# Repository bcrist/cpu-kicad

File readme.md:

This repo contains KiCAD design files for my hobby discrete-logic CPU.

You can find the main repo here: https://github.com/bcrist/cpu

This repo is kept separately because KiCAD files tend to get very large, and I want to be able to ensure that the main repo doesn't get bloated with them.  The main repo instead has this repo as a shallow submodule.  Yes, I could have just used LFS instead, but I'd rather it be completely separate.

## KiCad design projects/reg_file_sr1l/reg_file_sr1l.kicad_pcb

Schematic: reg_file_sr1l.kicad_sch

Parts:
C1, C6: 10u; C_0805
C2, C5, C7, C10: 100n; C_0402
C3, C4, C8, C9: 22u; C_0805
J1, J2, J3: 2M11_2M71; CardEdge_PCIe_x16
L1, L2: 3.3u; L_taiyo_yuden_nrs5040
Q1, Q2: 2N3904; U_TO92-3
R1: 33k2 1%; R_0402
R2, R6: 10k 1%; R_0402
R3, R7: LIST; R_0402
R4, R8: 15m; R_1206
R5: 56k2 1%; R_0402
R9, R10, R11, R12: 1k; R_0402
U1, U3: AP62300TWU-7; U_SOT23-6
U2, U4: EMC1702; U_QFN-12_4x4_P0.8_EP2.1x2.1
U5, U7, U24: 74LVC1G86; U_SOT353_1.25x2.1_P0.65
U6, U12: 74LVC1G157; U_SOT363_1.25x2.1_P0.65
U8, U9: CY7C0241-15AC; U_QFP-100_14x14_P0.5
U10: 74LVC139; U_TSSOP-16_4.4x5_P0.65
U11: 74LVC138; U_TSSOP-16_4.4x5_P0.65
U13: 74LVCH16244A; U_TVSOP-48_4.4x9.7_P0.4
U14, U15: 74LVT16244; U_TVSOP-48_4.4x9.7_P0.4
U16: 74LVCH16374; U_TSSOP-48_6.1x12.5_P0.5
U17, U18: 74LVC574; U_TSSOP-20_4.4x6.5_P0.65
U19, U20, U21, U22: 74LVC541; U_TSSOP-20_4.4x6.5_P0.65
U23: 74LVC1G02; U_SOT353_1.25x2.1_P0.65
U25: 74LVC1G332; U_SOT363_1.25x2.1_P0.65

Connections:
+5V: R8.1, U4.11 (SENSE-), U6.3, U8.12 (+5V), U8.17 (+5V), U8.36 (~ROE), U8.39 (~RSEM), U8.62 (M~S), U8.86 (~LSEM), U8.87 (~LWE), U8.88 (+5V), U9.12 (+5V), U9.17 (+5V), U9.36 (~ROE), U9.39 (~RSEM), U9.62 (M~S), U9.86 (~LSEM), U9.87 (~LWE), U9.88 (+5V), U11.6, U12.3
+12V: C1.1, C6.1, J1.A1, J1.A2, J1.A3, J1.B1, J1.B2, J1.B3, U1.3 (VIN), U3.3 (VIN)
/3v3: C3.1, C4.1, C5.1, L1.1, R1.1, R4.2, U2.1 (VDD), U2.12 (SENSE+)
/5v0: C8.1, C9.1, C10.1, L2.1, R5.1, R8.2, U4.1 (VDD), U4.12 (SENSE+)
/PHI: U16.25 (CLK), U16.48 (CLK), U17.11, U18.11, U25.3
/RD_{0}: U9.90 (LD0), U14.47 (A0), U15.47 (A0), U16.47 (A0)
/RD_{1}: U9.91 (LD1), U14.46 (A1), U15.46 (A1), U16.46 (A1)
/RD_{2}: U9.93 (LD2), U14.44 (A2), U15.44 (A2), U16.44 (A2)
/RD_{3}: U9.94 (LD3), U14.43 (A3), U15.43 (A3), U16.43 (A3)
/RD_{4}: U9.95 (LD4), U14.41 (A4), U15.41 (A4), U16.41 (A4)
/RD_{5}: U9.96 (LD5), U14.40 (A5), U15.40 (A5), U16.40 (A5)
/RD_{6}: U9.97 (LD6), U14.38 (A6), U15.38 (A6), U16.38 (A6)
/RD_{7}: U9.98 (LD7), U14.37 (A7), U15.37 (A7), U16.37 (A7)
/RD_{8}: U9.3 (LD8), U14.36 (A4), U15.36 (A4), U16.36 (A4)
/RD_{9}: U9.4 (LD17), U14.35 (A5), U15.35 (A5), U16.35 (A5)
/RD_{10}: U9.5 (LD11), U14.33 (A6), U15.33 (A6), U16.33 (A6)
/RD_{11}: U9.6 (LD12), U14.32 (A7), U15.32 (A7), U16.32 (A7)
/RD_{12}: U9.7 (LD13), U14.30 (A4), U15.30 (A4), U16.30 (A4)
/RD_{13}: U9.8 (LD14), U14.29 (A5), U15.29 (A5), U16.29 (A5)
/RD_{14}: U9.10 (LD15), U14.27 (A6), U15.27 (A6), U16.27 (A6)
/RD_{15}: U9.11 (LD16), U14.26 (A7), U15.26 (A7), U16.26 (A7)
/S.A_BASE_{0}: J1.A24, U13.2 (Y0)
/S.A_BASE_{1}: J1.A25, U13.3 (Y1)
/S.A_BASE_{2}: J1.A26, U13.5 (Y2)
/S.A_BASE_{3}: J1.A27, U13.6 (Y3)
/S.A_BASE_{4}: J1.A28, U13.8 (Y4)
/S.A_BASE_{5}: J1.A29, U13.9 (Y5)
/S.A_BASE_{6}: J1.A30, U13.11 (Y6)
/S.A_BASE_{7}: J1.A31, U13.12 (Y7)
/S.A_BASE_{8}: J1.A32, U13.13 (Y4)
/S.A_BASE_{9}: J1.A33, U13.14 (Y5)
/S.A_BASE_{10}: J1.A34, U13.16 (Y6)
/S.A_BASE_{11}: J1.A35, U13.17 (Y7)
/S.A_BASE_{12}: J1.A36, U13.19 (Y4)
/S.A_BASE_{13}: J1.A37, U13.20 (Y5)
/S.A_BASE_{14}: J1.A38, U13.22 (Y6)
/S.A_BASE_{15}: J1.A39, U13.23 (Y7)
/S.BASE_{0}: U8.66 (LA0)
/S.BASE_{1}: U8.67 (LA1)
/S.BASE_{2}: U8.68 (LA2)
/S.BASE_{3}: U6.6, U12.6
/S.FX_OVR_R_BASE: U5.1
/S.FX_OVR_R_SR1: U7.1
/S.FX_OVR_W: U24.1
/S.JL_SRC_{0}: U10.2
/S.JL_SRC_{1}: U10.3
/S.JL_{0}: J3.A57, U14.2 (Y0)
/S.JL_{1}: J3.A56, U14.3 (Y1)
/S.JL_{2}: J3.A55, U14.5 (Y2)
/S.JL_{3}: J3.A54, U14.6 (Y3)
/S.JL_{4}: J3.A53, U14.8 (Y4)
/S.JL_{5}: J3.A52, U14.9 (Y5)
/S.JL_{6}: J3.A51, U14.11 (Y6)
/S.JL_{7}: J3.A50, U14.12 (Y7)
/S.JL_{8}: J3.A49, U14.13 (Y4)
/S.JL_{9}: J3.A48, U14.14 (Y5)
/S.JL_{10}: J3.A47, U14.16 (Y6)
/S.JL_{11}: J3.A46, U14.17 (Y7)
/S.JL_{12}: J3.A45, U14.19 (Y4)
/S.JL_{13}: J3.A44, U14.20 (Y5)
/S.JL_{14}: J3.A43, U14.22 (Y6)
/S.JL_{15}: J3.A42, U14.23 (Y7)
/S.K_SRC_{0}: U11.1
/S.K_SRC_{1}: U11.2
/S.K_SRC_{2}: U11.3
/S.K_{0}: J3.A35, U15.2 (Y0)
/S.K_{1}: J3.A34, U15.3 (Y1)
/S.K_{2}: J3.A33, U15.5 (Y2)
/S.K_{3}: J3.A32, U15.6 (Y3)
/S.K_{4}: J3.A31, U15.8 (Y4)
/S.K_{5}: J3.A30, U15.9 (Y5)
/S.K_{6}: J3.A29, U15.11 (Y6)
/S.K_{7}: J3.A28, U15.12 (Y7)
/S.K_{8}: J3.A27, U15.13 (Y4)
/S.K_{9}: J3.A26, U15.14 (Y5)
/S.K_{10}: J3.A25, U15.16 (Y6)
/S.K_{11}: J3.A24, U15.17 (Y7)
/S.K_{12}: J3.A23, U15.19 (Y4)
/S.K_{13}: J3.A22, U15.20 (Y5)
/S.K_{14}: J3.A21, U15.22 (Y6)
/S.K_{15}: J3.A20, U15.23 (Y7)
/S.RCTX_{0}: U8.69 (LA3), U9.69 (LA3)
/S.RCTX_{1}: U8.70 (LA4), U9.70 (LA4)
/S.RCTX_{2}: U8.71 (LA5), U9.71 (LA5)
/S.RCTX_{3}: U8.76 (LA6), U9.76 (LA6)
/S.RCTX_{4}: U8.77 (LA7), U9.77 (LA7)
/S.RCTX_{5}: U8.78 (LA8), U9.78 (LA8)
/S.SR1_RI_{0}: U9.66 (LA0)
/S.SR1_RI_{1}: U9.67 (LA1)
/S.SR1_RI_{2}: U9.68 (LA2)
/SCL: J1.B5, U2.8 (SCL), U4.8 (SCL)
/SDA: J1.B6, U2.7 (SDA), U4.7 (SDA)
/SLEEPING: U6.1, U8.40 (~RCE), U9.40 (~RCE), U9.85 (~LCE)
/SW3v3: C2.2, L1.2, U1.2 (SW)
/SW5v0: C7.2, L2.2, U3.2 (SW)
/T.INHIBIT_W: U25.1
/T.L_{0}: J2.A61, U19.2 (A0)
/T.L_{1}: J2.A60, U19.3 (A1)
/T.L_{2}: J2.A59, U19.4 (A2)
/T.L_{3}: J2.A58, U19.5 (A3)
/T.L_{4}: J2.A57, U19.6 (A4)
/T.L_{5}: J2.A56, U19.7 (A5)
/T.L_{6}: J2.A55, U19.8 (A6)
/T.L_{7}: J2.A54, U19.9 (A7)
/T.L_{8}: J2.A53, U20.2 (A0)
/T.L_{9}: J2.A52, U20.3 (A1)
/T.L_{10}: J2.A51, U20.4 (A2)
/T.L_{11}: J2.A50, U20.5 (A3)
/T.L_{12}: J2.A49, U20.6 (A4)
/T.L_{13}: J2.A48, U20.7 (A5)
/T.L_{14}: J2.A47, U20.8 (A6)
/T.L_{15}: J2.A46, U20.9 (A7)
/T.N_{0}: J1.A53, U21.2 (A0)
/T.N_{1}: J1.A54, U21.3 (A1)
/T.N_{2}: J1.A55, U21.4 (A2)
/T.N_{3}: J1.A56, U21.5 (A3)
/T.N_{4}: J1.A57, U21.6 (A4)
/T.N_{5}: J1.A58, U21.7 (A5)
/T.N_{6}: J1.A59, U21.8 (A6)
/T.N_{7}: J1.A60, U21.9 (A7)
/T.N_{8}: J1.A61, U22.2 (A0)
/T.N_{9}: J1.A62, U22.3 (A1)
/T.N_{10}: J1.A63, U22.4 (A2)
/T.N_{11}: J1.A64, U22.5 (A3)
/T.P_{0}: J1.A65, U22.6 (A4)
/T.P_{1}: J1.A66, U22.7 (A5)
/T.P_{2}: J1.A67, U22.8 (A6)
/T.P_{3}: J1.A68, U22.9 (A7)
/T.RCTX_{0}: U8.56 (RA3), U9.56 (RA3)
/T.RCTX_{1}: U8.55 (RA4), U9.55 (RA4)
/T.RCTX_{2}: U8.50 (RA5), U9.50 (RA5)
/T.RCTX_{3}: U8.49 (RA6), U9.49 (RA6)
/T.RCTX_{4}: U8.48 (RA7), U9.48 (RA7)
/T.RCTX_{5}: U8.47 (RA8), U9.47 (RA8)
/T.SR1_WI_{0}: U8.59 (RA0), U9.59 (RA0)
/T.SR1_WI_{1}: U8.58 (RA1), U9.58 (RA1)
/T.SR1_WI_{2}: U8.57 (RA2), U9.57 (RA2)
/T.SR1_WSRC_{0}: U10.14, U23.1
/T.SR1_WSRC_{1}: U10.13, U23.2
/WD_{0}: U8.14 (RD0), U9.14 (RD0), U17.19 (Q0), U19.18 (Y0), U21.18 (Y0)
/WD_{1}: U8.15 (RD1), U9.15 (RD1), U17.18 (Q1), U19.17 (Y1), U21.17 (Y1)
/WD_{2}: U8.16 (RD2), U9.16 (RD2), U17.17 (Q2), U19.16 (Y2), U21.16 (Y2)
/WD_{3}: U8.18 (RD3), U9.18 (RD3), U17.16 (Q3), U19.15 (Y3), U21.15 (Y3)
/WD_{4}: U8.19 (RD4), U9.19 (RD4), U17.15 (Q4), U19.14 (Y4), U21.14 (Y4)
/WD_{5}: U8.20 (RD5), U9.20 (RD5), U17.14 (Q5), U19.13 (Y5), U21.13 (Y5)
/WD_{6}: U8.21 (RD6), U9.21 (RD6), U17.13 (Q6), U19.12 (Y6), U21.12 (Y6)
/WD_{7}: U8.26 (RD7), U9.26 (RD7), U17.12 (Q7), U19.11 (Y7), U21.11 (Y7)
/WD_{8}: U8.22 (RD8), U9.22 (RD8), U18.19 (Q0), U20.18 (Y0), U22.18 (Y0)
/WD_{9}: U8.23 (RD17), U9.23 (RD17), U18.18 (Q1), U20.17 (Y1), U22.17 (Y1)
/WD_{10}: U8.29 (RD11), U9.29 (RD11), U18.17 (Q2), U20.16 (Y2), U22.16 (Y2)
/WD_{11}: U8.30 (RD12), U9.30 (RD12), U18.16 (Q3), U20.15 (Y3), U22.15 (Y3)
/WD_{12}: U8.31 (RD13), U9.31 (RD13), U18.15 (Q4), U20.14 (Y4), U22.14 (Y4)
/WD_{13}: U8.32 (RD14), U9.32 (RD14), U18.14 (Q5), U20.13 (Y5), U22.13 (Y5)
/WD_{14}: U8.33 (RD15), U9.33 (RD15), U18.13 (Q6), U20.12 (Y6), U22.12 (Y6)
/WD_{15}: U8.35 (RD16), U9.35 (RD16), U18.12 (Q7), U20.11 (Y7), U22.11 (Y7)
/WFX: U8.46 (RA9), U9.46 (RA9), U24.4
/~PHI: U10.1, U11.4, U12.1
/~RESETod: J1.A7
/~WE: U8.37 (~RWE), U9.37 (~RWE), U25.4
/~WRITE_FROM_L: U10.10, U19.1 (~OE), U20.1 (~OE)
/~WRITE_FROM_PN: U10.9, U21.1 (~OE), U22.1 (~OE)
/~WRITE_FROM_SELF: U10.11, U17.1 (~OE), U18.1 (~OE)
GND: C1.2, C3.2, C4.2, C5.2, C6.2, C8.2, C9.2, C10.2, J1.A4, J1.A5, J1.A6, J1.B4, J1.B7, R2.2, R3.2, R6.2, R7.2, R9.2, R10.2, R11.2, R12.2, U1.1 (GND), U2.EP (GND), U3.1 (GND), U4.EP (GND), U5.3 (GND), U6.2 (GND), U7.3 (GND), U8.9 (GND), U8.13 (GND), U8.34 (GND), U8.38 (GND), U8.41 (~RHE), U8.42 (~RLE), U8.44 (RA11), U8.45 (RA10), U8.63 (GND), U8.80 (LA10), U8.81 (LA11), U8.83 (~LLE), U8.84 (~LHE), U8.89 (~LOE), U8.92 (GND), U9.9 (GND), U9.13 (GND), U9.34 (GND), U9.38 (GND), U9.41 (~RHE), U9.42 (~RLE), U9.44 (RA11), U9.45 (RA10), U9.63 (GND), U9.80 (LA10), U9.81 (LA11), U9.83 (~LLE), U9.84 (~LHE), U9.89 (~LOE), U9.92 (GND), U10.8 (GND), U10.15, U11.5, U11.8 (GND), U12.2 (GND), U13.4 (GND), U13.10 (GND), U13.15 (GND), U13.21 (GND), U13.28 (GND), U13.34 (GND), U13.39 (GND), U13.45 (GND), U14.4 (GND), U14.10 (GND), U14.15 (GND), U14.21 (GND), U14.28 (GND), U14.34 (GND), U14.39 (GND), U14.45 (GND), U15.4 (GND), U15.10 (GND), U15.15 (GND), U15.21 (GND), U15.28 (GND), U15.34 (GND), U15.39 (GND), U15.45 (GND), U16.1 (~OE), U16.4 (GND), U16.10 (GND), U16.15 (GND), U16.21 (GND), U16.24 (~OE), U16.28 (GND), U16.34 (GND), U16.39 (GND), U16.45 (GND), U17.10 (GND), U18.10 (GND), U19.10 (GND), U19.19 (~OE), U20.10 (GND), U20.19 (~OE), U21.10 (GND), U21.19 (~OE), U22.10 (GND), U22.19 (~OE), U23.3 (GND), U24.3 (GND), U25.2 (GND)
unnamed: C2.1, U1.6 (BST)
unnamed: C7.1, U3.6 (BST)
unnamed: Q1.1 (E), U2.3 (DN)
unnamed: Q1.2 (B), Q1.3 (C), U2.2 (DP)
unnamed: Q2.1 (E), U4.3 (DN)
unnamed: Q2.2 (B), Q2.3 (C), U4.2 (DP)
unnamed: R1.2, R2.1, U1.4 (FB)
unnamed: R3.1, U2.4 (ADDR)
unnamed: R5.2, R6.1, U3.4 (FB)
unnamed: R7.1, U4.4 (ADDR)
unnamed: R9.1, U8.27 (RD9)
unnamed: R10.1, U8.28 (RD10)
unnamed: R11.1, U9.27 (RD9)
unnamed: R12.1, U9.28 (RD10)
unnamed: U5.4, U8.79 (LA9)
unnamed: U6.4, U8.85 (~LCE)
unnamed: U7.4, U9.79 (LA9)
unnamed: U10.6, U14.1 (~OE), U14.24 (~OE), U14.25 (~OE), U14.48 (~OE)
unnamed: U11.13, U15.1 (~OE), U15.24 (~OE), U15.25 (~OE), U15.48 (~OE)
unnamed: U12.4, U13.1 (~OE), U13.24 (~OE), U13.25 (~OE), U13.48 (~OE)
unnamed: U8.11 (LD16), U13.26 (A7)
unnamed: U8.10 (LD15), U13.27 (A6)
unnamed: U8.8 (LD14), U13.29 (A5)
unnamed: U8.7 (LD13), U13.30 (A4)
unnamed: U8.6 (LD12), U13.32 (A7)
unnamed: U8.5 (LD11), U13.33 (A6)
unnamed: U8.4 (LD17), U13.35 (A5)
unnamed: U8.3 (LD8), U13.36 (A4)
unnamed: U8.98 (LD7), U13.37 (A7)
unnamed: U8.97 (LD6), U13.38 (A6)
unnamed: U8.96 (LD5), U13.40 (A5)
unnamed: U8.95 (LD4), U13.41 (A4)
unnamed: U8.94 (LD3), U13.43 (A3)
unnamed: U8.93 (LD2), U13.44 (A2)
unnamed: U8.91 (LD1), U13.46 (A1)
unnamed: U8.90 (LD0), U13.47 (A0)
unnamed: U16.2 (Y0), U17.2 (D0)
unnamed: U16.3 (Y1), U17.3 (D1)
unnamed: U16.5 (Y2), U17.4 (D2)
unnamed: U16.6 (Y3), U17.5 (D3)
unnamed: U16.8 (Y4), U17.6 (D4)
unnamed: U16.9 (Y5), U17.7 (D5)
unnamed: U16.11 (Y6), U17.8 (D6)
unnamed: U16.12 (Y7), U17.9 (D7)
unnamed: U16.13 (Y4), U18.2 (D0)
unnamed: U16.14 (Y5), U18.3 (D1)
unnamed: U16.16 (Y6), U18.4 (D2)
unnamed: U16.17 (Y7), U18.5 (D3)
unnamed: U16.19 (Y4), U18.6 (D4)
unnamed: U16.20 (Y5), U18.7 (D5)
unnamed: U16.22 (Y6), U18.8 (D6)
unnamed: U16.23 (Y7), U18.9 (D7)
unnamed: U23.4, U25.6
VCC: R4.1, U2.11 (SENSE-), U5.5 (VCC), U6.5 (VCC), U7.5 (VCC), U10.16 (VCC), U11.16 (VCC), U12.5 (VCC), U13.7 (VCC), U13.18 (VCC), U13.31 (VCC), U13.42 (VCC), U14.7 (VCC), U14.18 (VCC), U14.31 (VCC), U14.42 (VCC), U15.7 (VCC), U15.18 (VCC), U15.31 (VCC), U15.42 (VCC), U16.7 (VCC), U16.18 (VCC), U16.31 (VCC), U16.42 (VCC), U17.20 (VCC), U18.20 (VCC), U19.20 (VCC), U20.20 (VCC), U21.20 (VCC), U22.20 (VCC), U23.5 (VCC), U24.5 (VCC), U25.5 (VCC)

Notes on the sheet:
Taiyo Yuden NRS5040T3R3NMGJ
LIST (5%) 0 100 180 300 430 560 750 1k27 1k6 2k 2k7 3k6 5k6 open
Susumu KRL1632E-M-R015-F-T5
TL = TQ
Address 0x4C 0x4D 0x4E 0x4F 0x48 0x49 0x4A 0x4B 0x28 0x29 0x2A 0x2B 0x2C 0x18

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
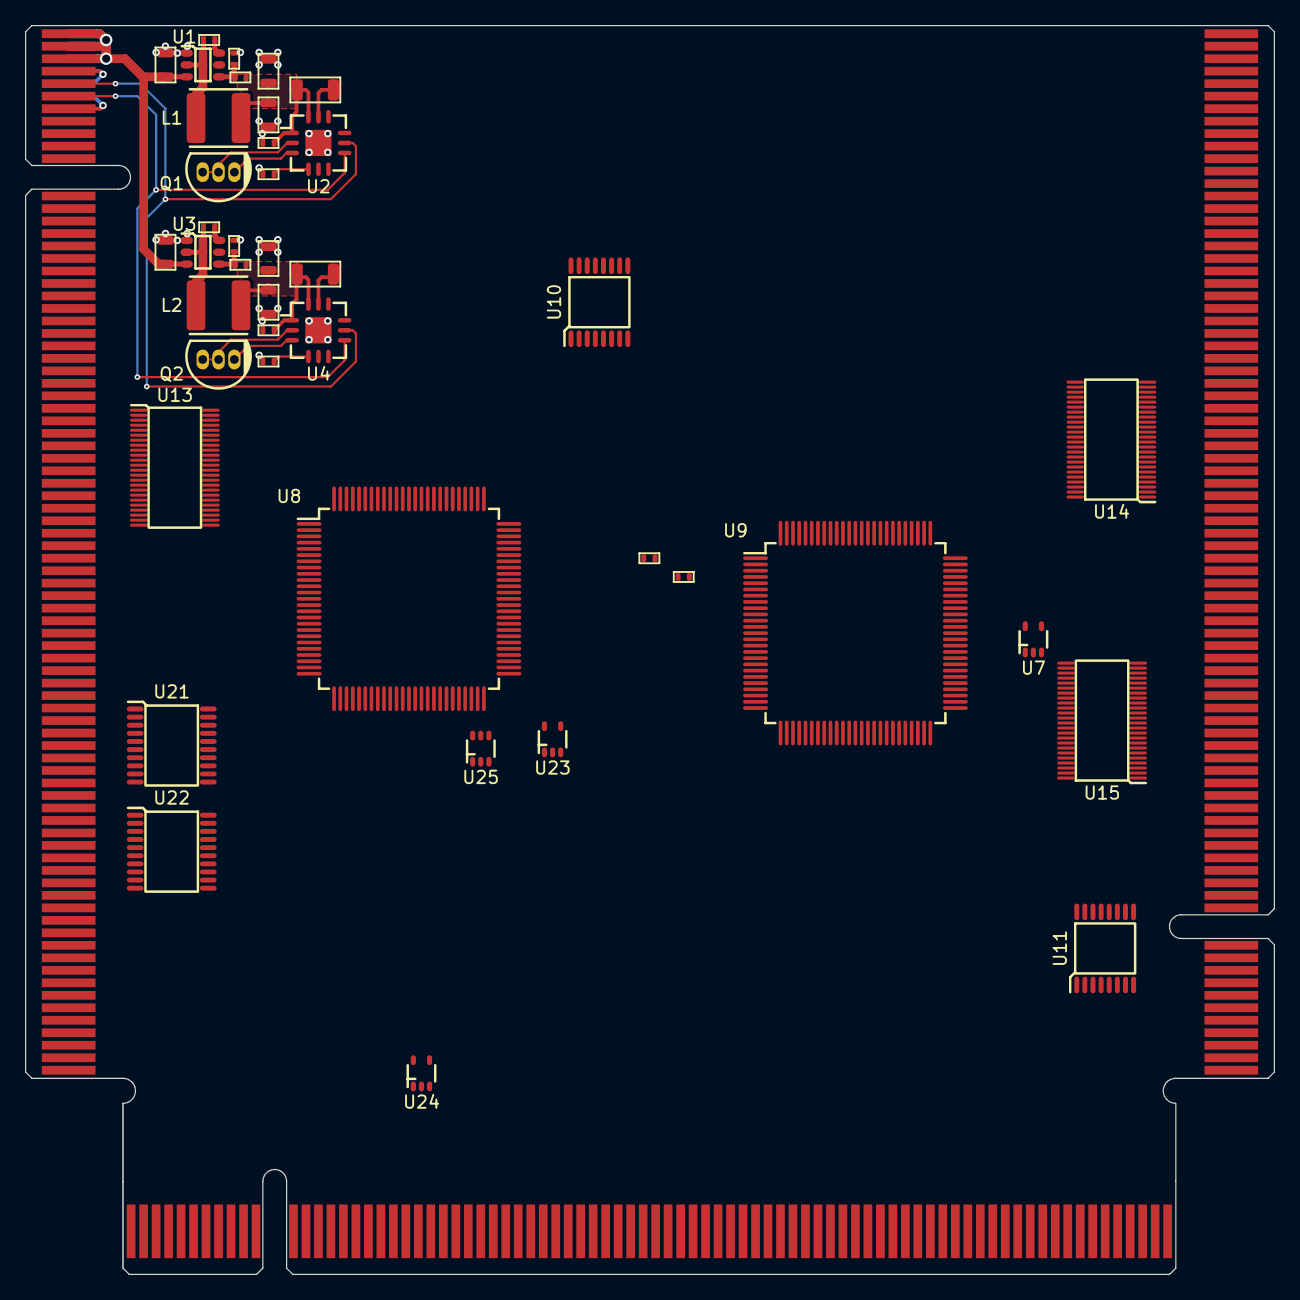
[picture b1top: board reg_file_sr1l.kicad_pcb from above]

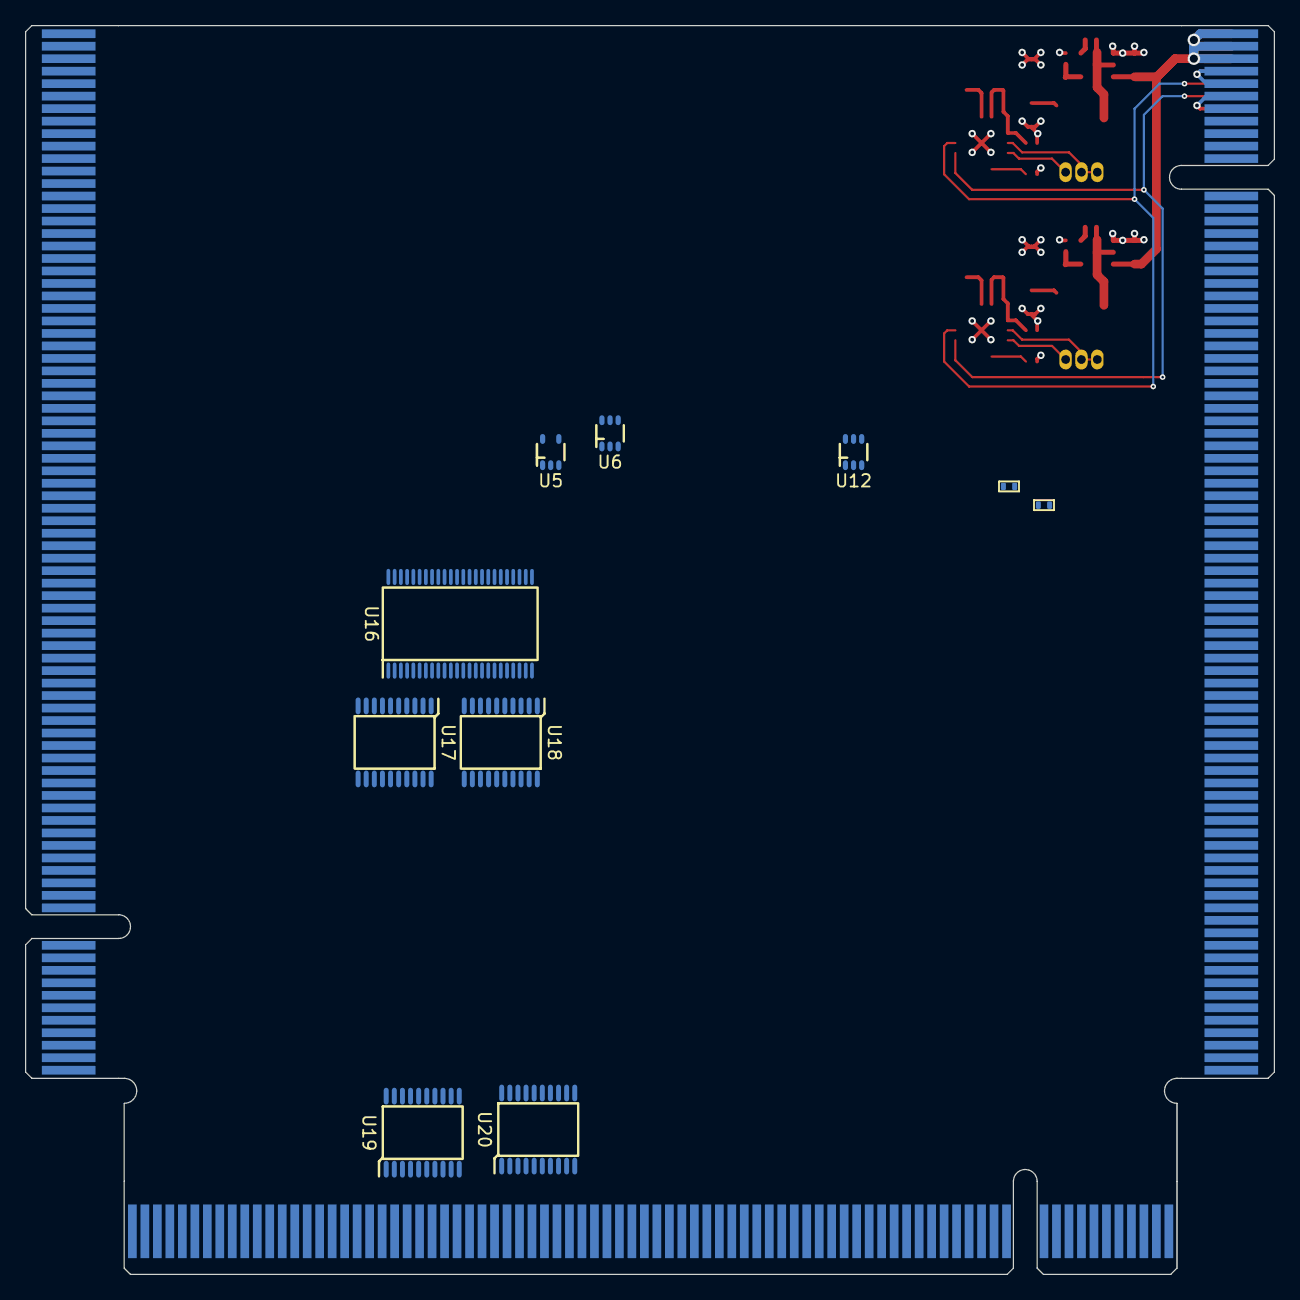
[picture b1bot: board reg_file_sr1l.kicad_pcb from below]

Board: 4 copper layers, 100.0 x 100.0 mm, 54 parts (10 on the bottom side), 202 nets.

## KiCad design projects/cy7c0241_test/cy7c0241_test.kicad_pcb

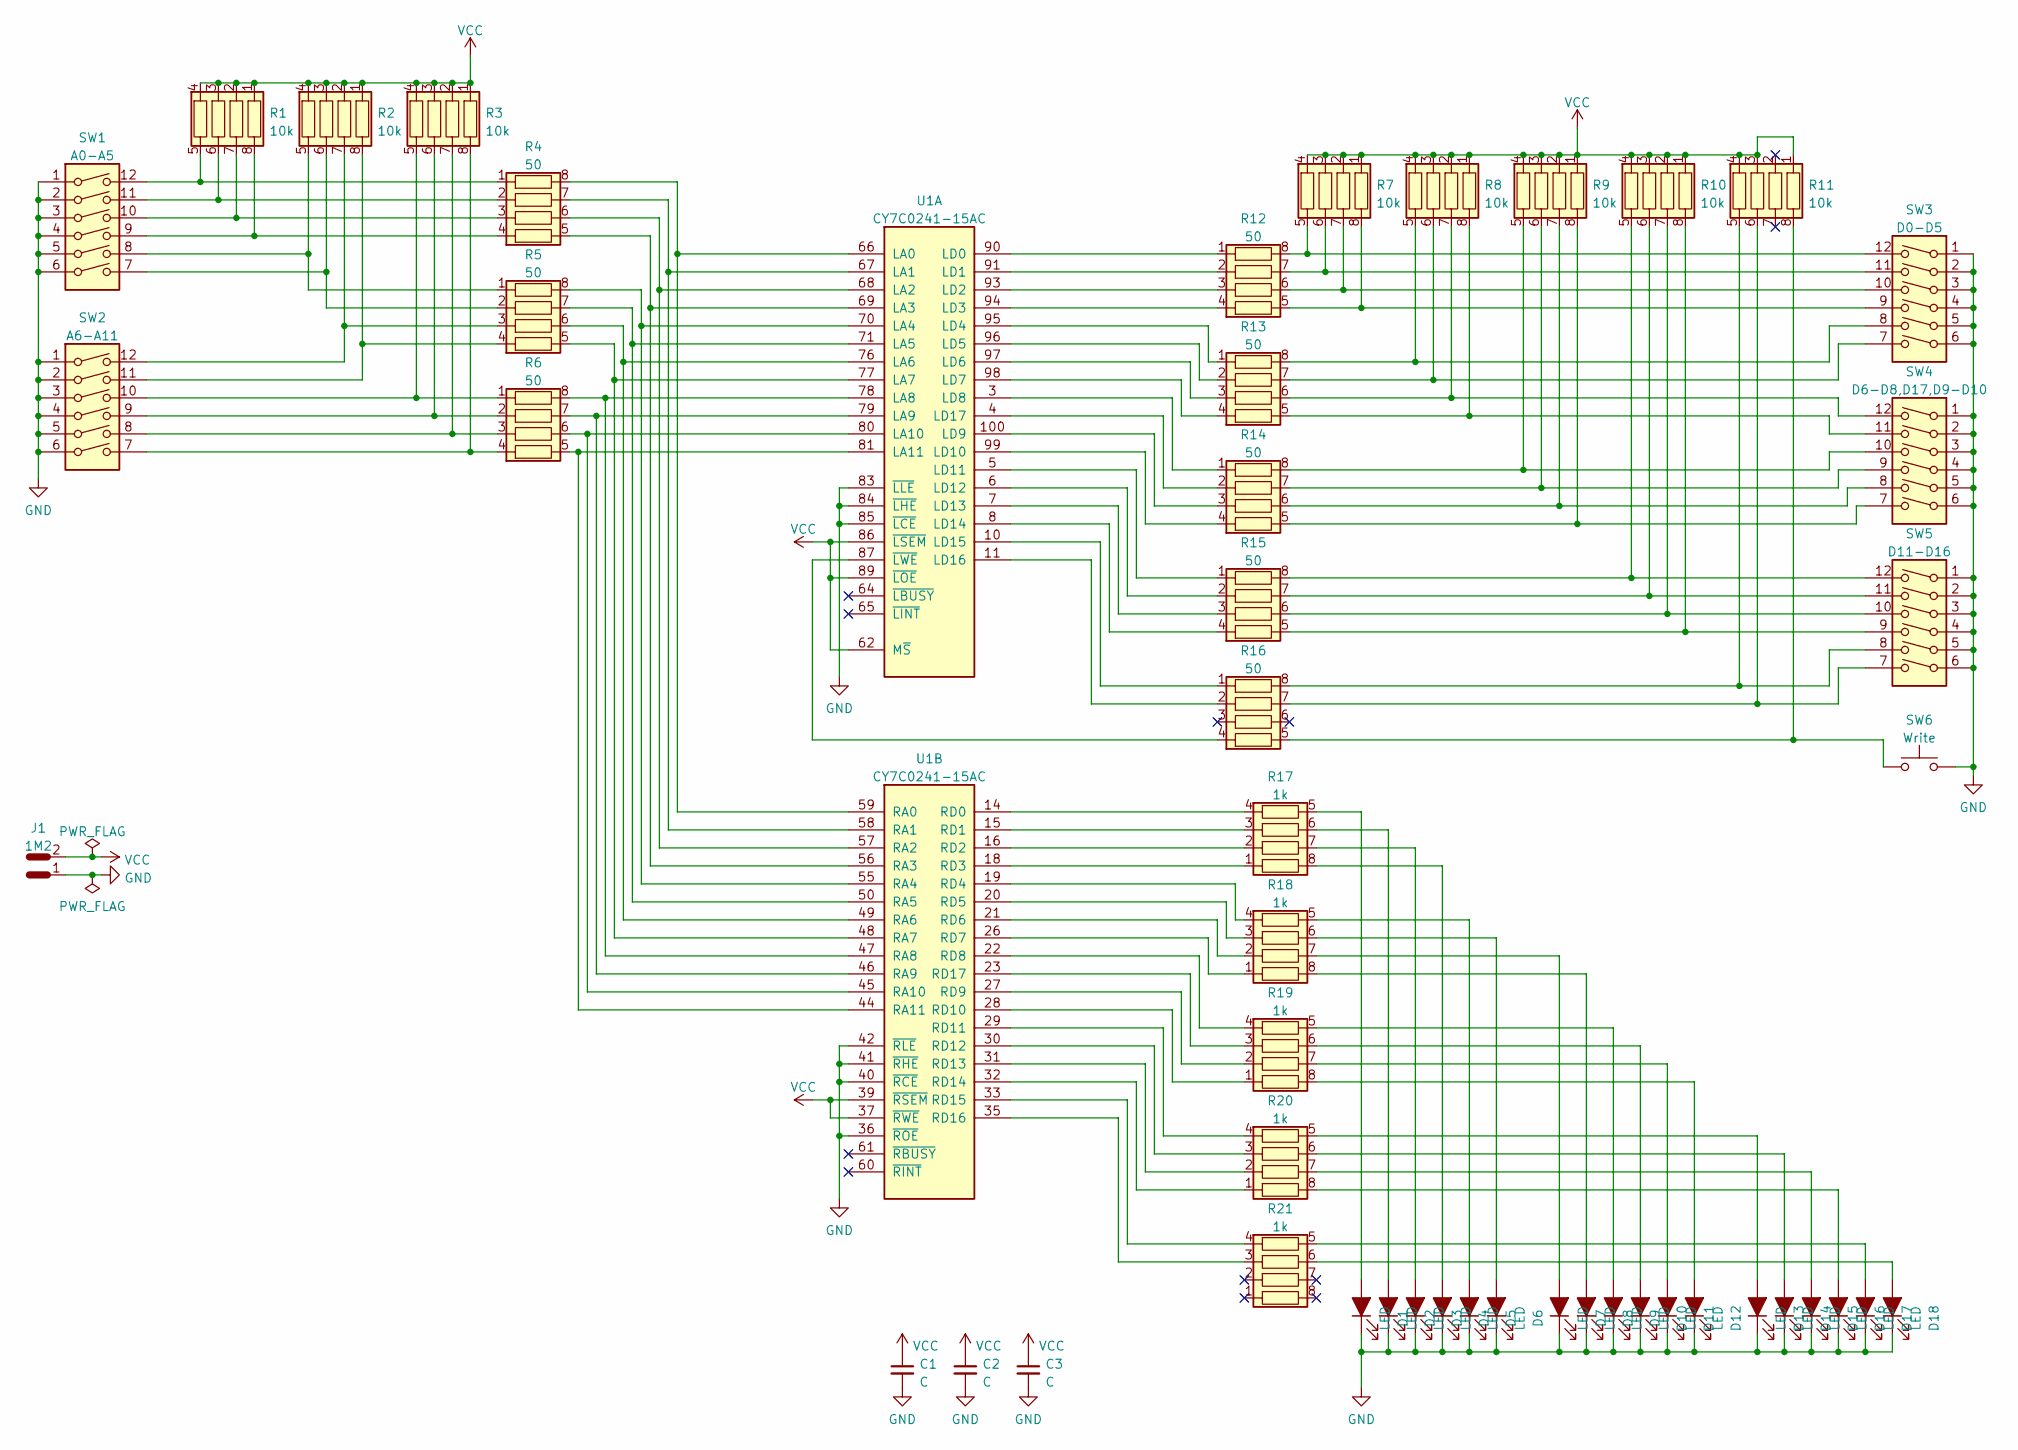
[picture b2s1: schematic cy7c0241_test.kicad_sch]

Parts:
C1, C2, C3: C; C_0603
D1, D2, D3, D4, D5, D6, D7, D8, D9, D10, D11, D12, D13, D14, D15, D16, D17, D18: LED; LED_0603
J1: 1M2; header_1x2
R1, R2, R3, R7, R8, R9, R10, R11: 10k; R_0408-8
R4, R5, R6, R12, R13, R14, R15, R16: 50; R_0408-8
R17, R18, R19, R20, R21: 1k; R_0408-8
SW1: A0-A5; SW_DIP-12_300mil
SW2: A6-A11; SW_DIP-12_300mil
SW3: D0-D5; SW_DIP-12_300mil
SW4: D6-D8,D17,D9-D10; SW_DIP-12_300mil
SW5: D11-D16; SW_DIP-12_300mil
SW6: Write; SW_Cherry_MX1A_1.00u_PCB_Centered
U1: CY7C0241-15AC; U_QFP-100_14x14_P0.5

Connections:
GND: C1.2, C2.2, C3.2, D1.1 (K), D2.1 (K), D3.1 (K), D4.1 (K), D5.1 (K), D6.1 (K), D7.1 (K), D8.1 (K), D9.1 (K), D10.1 (K), D11.1 (K), D12.1 (K), D13.1 (K), D14.1 (K), D15.1 (K), D16.1 (K), D17.1 (K), D18.1 (K), J1.1, SW1.1, SW1.2, SW1.3, SW1.4, SW1.5, SW1.6, SW2.1, SW2.2, SW2.3, SW2.4, SW2.5, SW2.6, SW3.1, SW3.2, SW3.3, SW3.4, SW3.5, SW3.6, SW4.1, SW4.2, SW4.3, SW4.4, SW4.5, SW4.6, SW5.1, SW5.2, SW5.3, SW5.4, SW5.5, SW5.6, SW6.2, U1.9 (GND), U1.13 (GND), U1.34 (GND), U1.36 (~ROE), U1.38 (GND), U1.40 (~RCE), U1.41 (~RHE), U1.42 (~RLE), U1.63 (GND), U1.83 (~LLE), U1.84 (~LHE), U1.85 (~LCE), U1.92 (GND)
unnamed: D5.2 (A), R18.5
unnamed: D6.2 (A), R18.6
unnamed: D7.2 (A), R18.7
unnamed: D8.2 (A), R18.8
unnamed: D9.2 (A), R19.5
unnamed: R1.5, R4.1, SW1.12
unnamed: R1.6, R4.2, SW1.11
unnamed: R1.7, R4.3, SW1.10
unnamed: R1.8, R4.4, SW1.9
unnamed: R2.5, R5.1, SW1.8
unnamed: R2.6, R5.2, SW1.7
unnamed: R2.7, R5.3, SW2.12
unnamed: R2.8, R5.4, SW2.11
unnamed: R3.5, R6.1, SW2.10
unnamed: R3.6, R6.2, SW2.9
unnamed: R3.7, R6.3, SW2.8
unnamed: R3.8, R6.4, SW2.7
unnamed: R8.5, R13.8, SW3.8
unnamed: R8.6, R13.7, SW3.7
unnamed: R10.5, R15.8, SW5.12
unnamed: R10.6, R15.7, SW5.11
unnamed: R10.7, R15.6, SW5.10
unnamed: R10.8, R15.5, SW5.9
unnamed: R11.5, R16.8, SW5.8
unnamed: R11.6, R16.7, SW5.7
unnamed: R11.8, R16.5, SW6.1
unnamed: R7.8, R12.5, SW3.9
unnamed: R7.7, R12.6, SW3.10
unnamed: R7.6, R12.7, SW3.11
unnamed: R7.5, R12.8, SW3.12
unnamed: R13.1, U1.95 (LD4)
unnamed: R13.2, U1.96 (LD5)
unnamed: R8.8, R13.5, SW4.11
unnamed: R8.7, R13.6, SW4.12
unnamed: R9.8, R14.5, SW4.7
unnamed: R9.7, R14.6, SW4.8
unnamed: R9.6, R14.7, SW4.9
unnamed: R9.5, R14.8, SW4.10
unnamed: D1.2 (A), R17.5
unnamed: D2.2 (A), R17.6
unnamed: D3.2 (A), R17.7
unnamed: D4.2 (A), R17.8
unnamed: D10.2 (A), R19.6
unnamed: D11.2 (A), R19.7
unnamed: D12.2 (A), R19.8
unnamed: D13.2 (A), R20.5
unnamed: D14.2 (A), R20.6
unnamed: D15.2 (A), R20.7
unnamed: D16.2 (A), R20.8
unnamed: D17.2 (A), R21.5
unnamed: D18.2 (A), R21.6
unnamed: R14.1, U1.3 (LD8)
unnamed: R14.2, U1.4 (LD17)
unnamed: R15.1, U1.5 (LD11)
unnamed: R15.2, U1.6 (LD12)
unnamed: R15.3, U1.7 (LD13)
unnamed: R15.4, U1.8 (LD14)
unnamed: R16.1, U1.10 (LD15)
unnamed: R16.2, U1.11 (LD16)
unnamed: R17.4, U1.14 (RD0)
unnamed: R17.3, U1.15 (RD1)
unnamed: R17.2, U1.16 (RD2)
unnamed: R17.1, U1.18 (RD3)
unnamed: R18.4, U1.19 (RD4)
unnamed: R18.3, U1.20 (RD5)
unnamed: R18.2, U1.21 (RD6)
unnamed: R19.4, U1.22 (RD8)
unnamed: R19.3, U1.23 (RD17)
unnamed: R18.1, U1.26 (RD7)
unnamed: R19.2, U1.27 (RD9)
unnamed: R19.1, U1.28 (RD10)
unnamed: R20.4, U1.29 (RD11)
unnamed: R20.3, U1.30 (RD12)
unnamed: R20.2, U1.31 (RD13)
unnamed: R20.1, U1.32 (RD14)
unnamed: R21.4, U1.33 (RD15)
unnamed: R21.3, U1.35 (RD16)
unnamed: R4.8, U1.59 (RA0), U1.66 (LA0)
unnamed: R4.7, U1.58 (RA1), U1.67 (LA1)
unnamed: R4.6, U1.57 (RA2), U1.68 (LA2)
unnamed: R4.5, U1.56 (RA3), U1.69 (LA3)
unnamed: R5.8, U1.55 (RA4), U1.70 (LA4)
unnamed: R5.7, U1.50 (RA5), U1.71 (LA5)
unnamed: R5.6, U1.49 (RA6), U1.76 (LA6)
unnamed: R5.5, U1.48 (RA7), U1.77 (LA7)
unnamed: R6.8, U1.47 (RA8), U1.78 (LA8)
unnamed: R6.7, U1.46 (RA9), U1.79 (LA9)
unnamed: R6.6, U1.45 (RA10), U1.80 (LA10)
unnamed: R6.5, U1.44 (RA11), U1.81 (LA11)
unnamed: R16.4, U1.87 (~LWE)
unnamed: R12.1, U1.90 (LD0)
unnamed: R12.2, U1.91 (LD1)
unnamed: R12.3, U1.93 (LD2)
unnamed: R12.4, U1.94 (LD3)
unnamed: R13.3, U1.97 (LD6)
unnamed: R13.4, U1.98 (LD7)
unnamed: R14.4, U1.99 (LD10)
unnamed: R14.3, U1.100 (LD9)
VCC: C1.1, C2.1, C3.1, J1.2, R1.1, R1.2, R1.3, R1.4, R2.1, R2.2, R2.3, R2.4, R3.1, R3.2, R3.3, R3.4, R7.1, R7.2, R7.3, R7.4, R8.1, R8.2, R8.3, R8.4, R9.1, R9.2, R9.3, R9.4, R10.1, R10.2, R10.3, R10.4, R11.1, R11.3, R11.4, U1.12 (VCC), U1.17 (VCC), U1.37 (~RWE), U1.39 (~RSEM), U1.62 (M~S), U1.86 (~LSEM), U1.88 (VCC), U1.89 (~LOE)

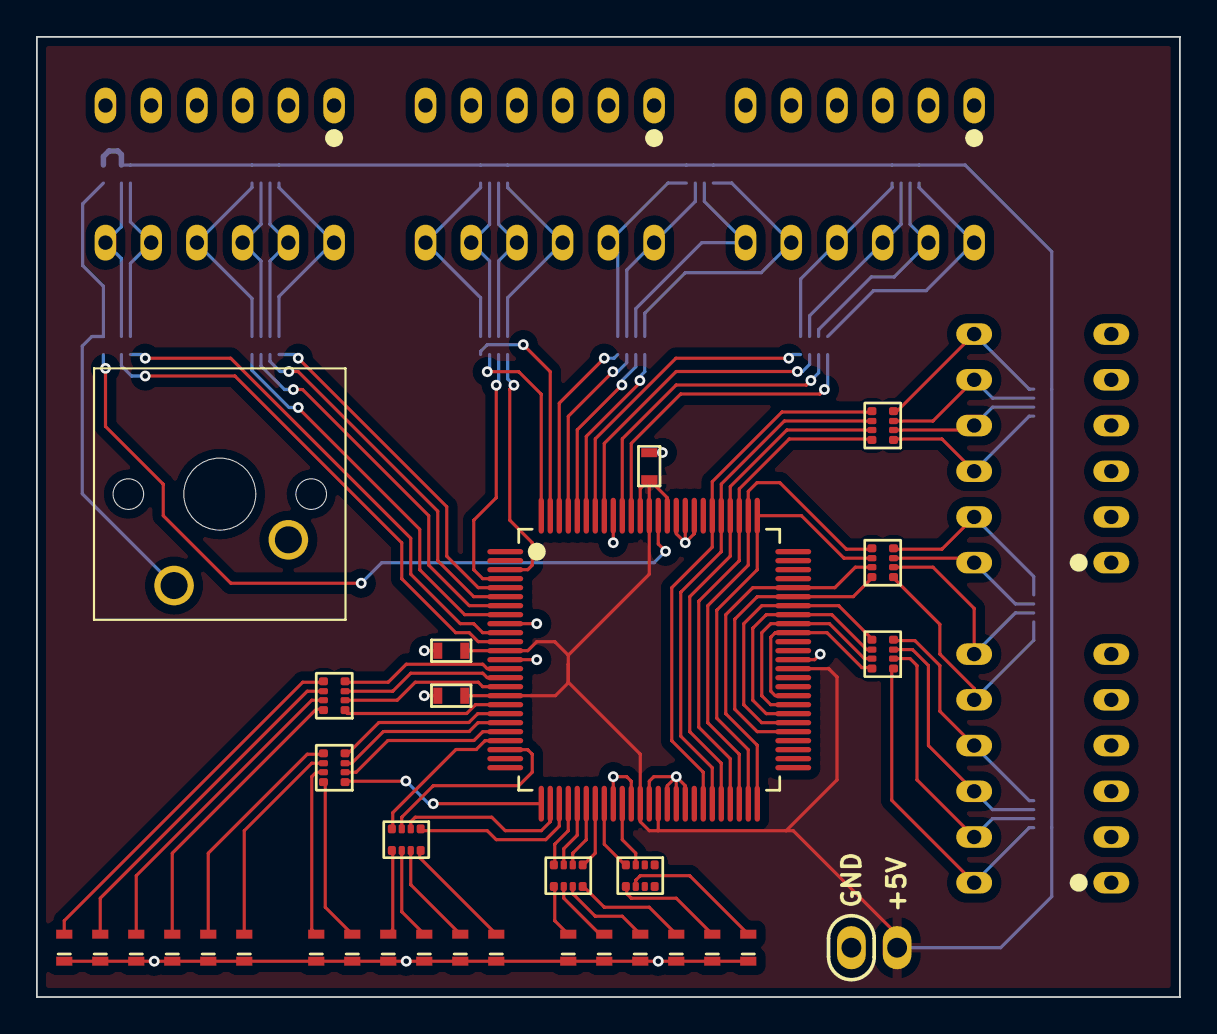
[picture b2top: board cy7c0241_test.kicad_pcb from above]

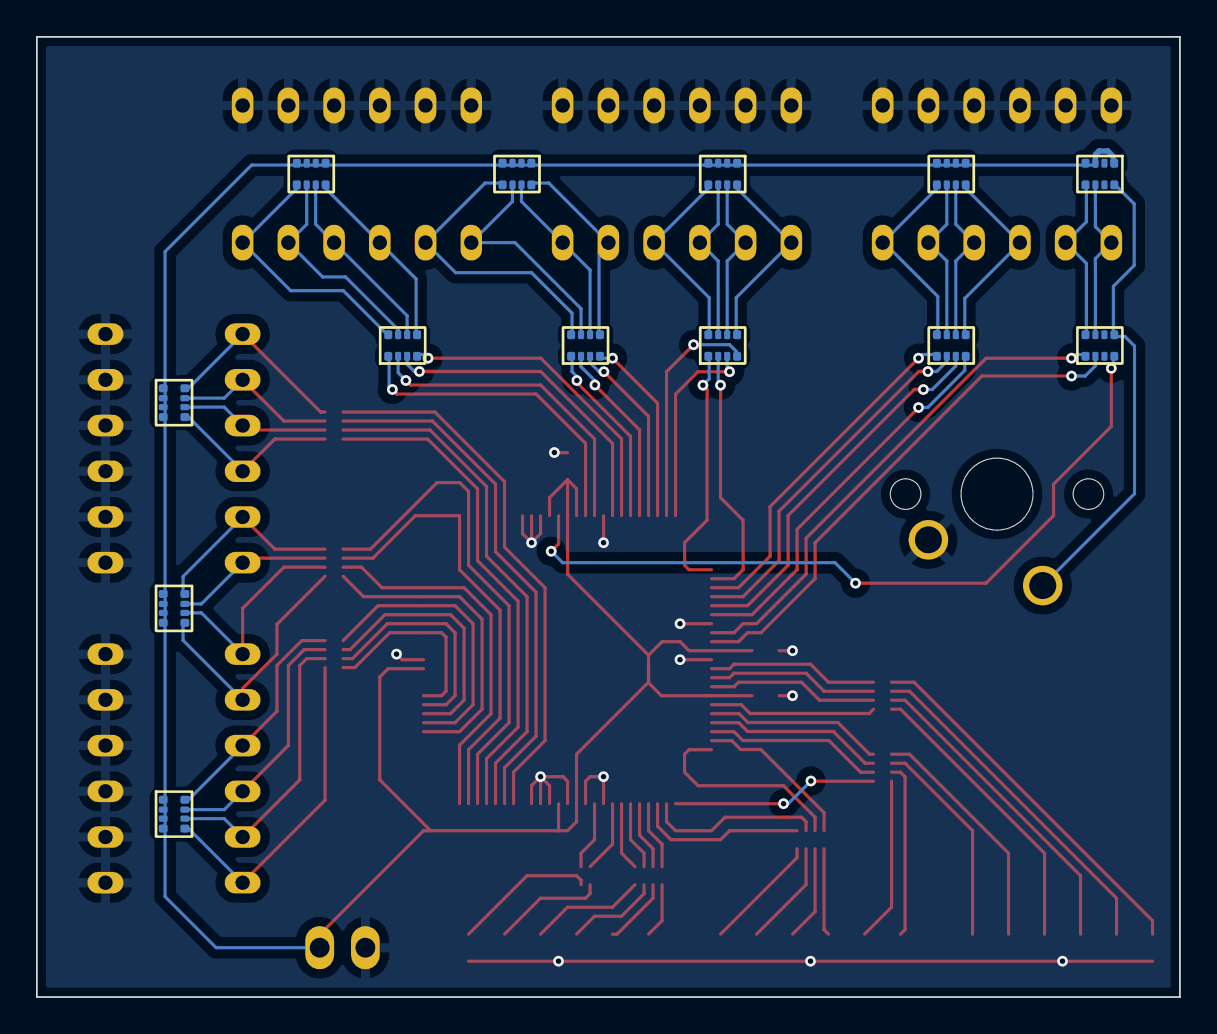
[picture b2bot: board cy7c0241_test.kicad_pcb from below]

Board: 4 copper layers, 63.5 x 53.3 mm, 50 parts (13 on the bottom side), 100 nets.

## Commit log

2023-02-27 kicad repo created
